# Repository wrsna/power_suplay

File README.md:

# power_suplay
This is just something I started one day and haven't finished it, now I am probably starting a different design because I need a power supply for my lab.

All files are created with Eagle software it is more or less schematic and board view and backup files

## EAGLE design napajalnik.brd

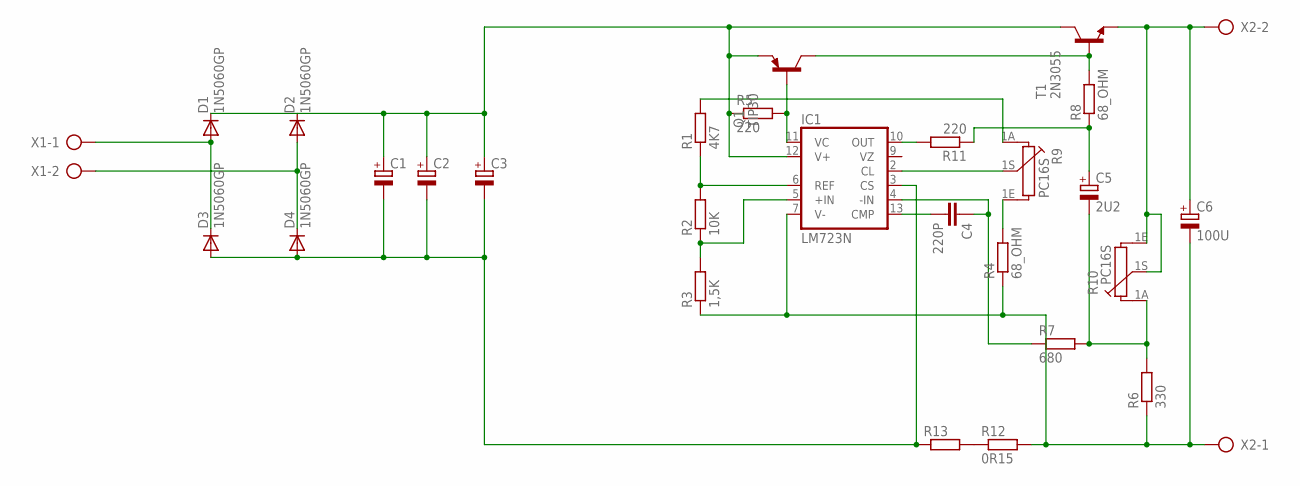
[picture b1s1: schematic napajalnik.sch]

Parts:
C1, C2, C3: CPOL-EUE10-20; EB20D
C4: 220P; C050-035X075
C5: 2U2; TAP5-45
C6: 100U; TAP5-80
D1, D2, D3, D4: 1N5060GP; DO15-12
IC1: LM723N; DIL14
Q1: TIP30; TO220
R1: 4K7; 0411/15
R2: 10K; 0411/15
R3: 1,5K; 0411/15
R4, R8: 68_OHM; 0411/15
R5, R11: 220; 0411/15
R6: 330; 0411/15
R7: 680; 0411/15
R9, R10: PC16S
R12: 0R15; 0411/15
R13: R-EU_0411/15; 0411/15
T1: 2N3055; TO3
X1, X2: AK300/2

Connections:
+: C6.+, R10.1E, R10.1S, T1.E, X2.2
GND1: C6.-, IC1.7 (V-), R3.1, R4.1, R6.1, R12.2, X2.1
unnamed: C1.+, C2.+, C3.+, D1.C, D2.C, IC1.12 (V+), Q1.3 (E), R5.1, T1.C, T1.C/ (C)
unnamed: D1.A, D3.C, X1.1
unnamed: D2.A, D4.C, X1.2
unnamed: C1.-, C2.-, C3.-, D3.A, D4.A, IC1.3 (CS), R13.1
unnamed: IC1.6 (REF), R1.1, R2.2
unnamed: IC1.5 (+IN), R2.1, R3.2
unnamed: C5.-, R6.2, R7.2, R10.1A
unnamed: R1.2, R9.1A
unnamed: R4.2, R9.1E
unnamed: IC1.11 (VC), Q1.1 (B), R5.2
unnamed: Q1.2 (C), R8.2, T1.B
unnamed: C4.1, IC1.4 (-IN), R7.1
unnamed: IC1.2 (CL), R9.1S
unnamed: C4.2, IC1.13 (CMP)
unnamed: IC1.10 (OUT), R11.2
unnamed: C5.+, R8.1, R11.1
unnamed: R12.1, R13.2

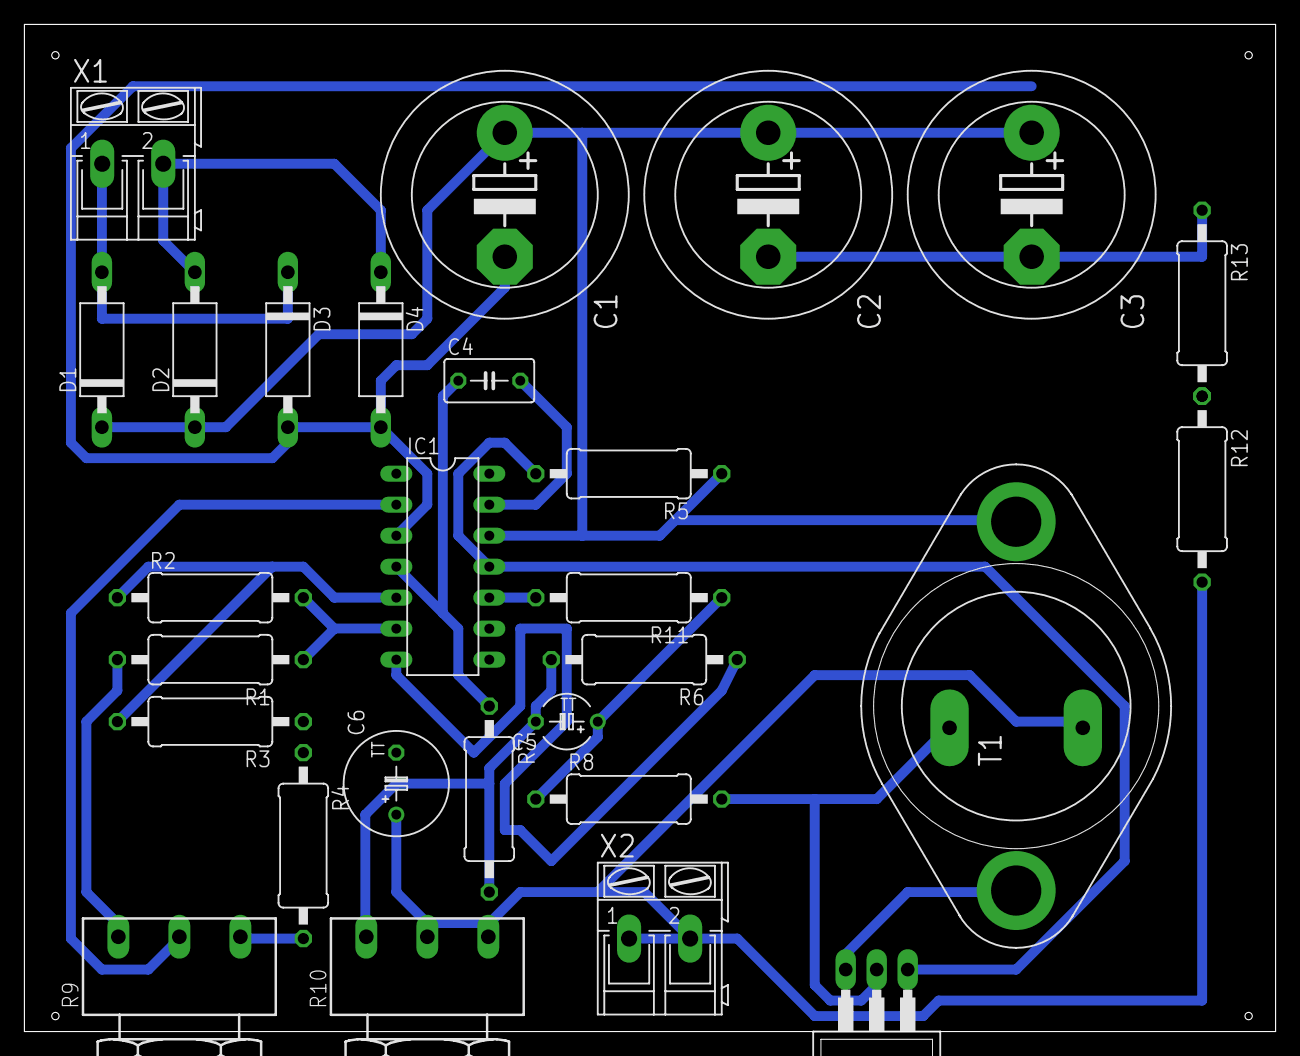
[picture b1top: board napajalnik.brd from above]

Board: 2 copper layers, 102.5 x 82.5 mm, 28 parts (0 on the bottom side), 19 nets.
